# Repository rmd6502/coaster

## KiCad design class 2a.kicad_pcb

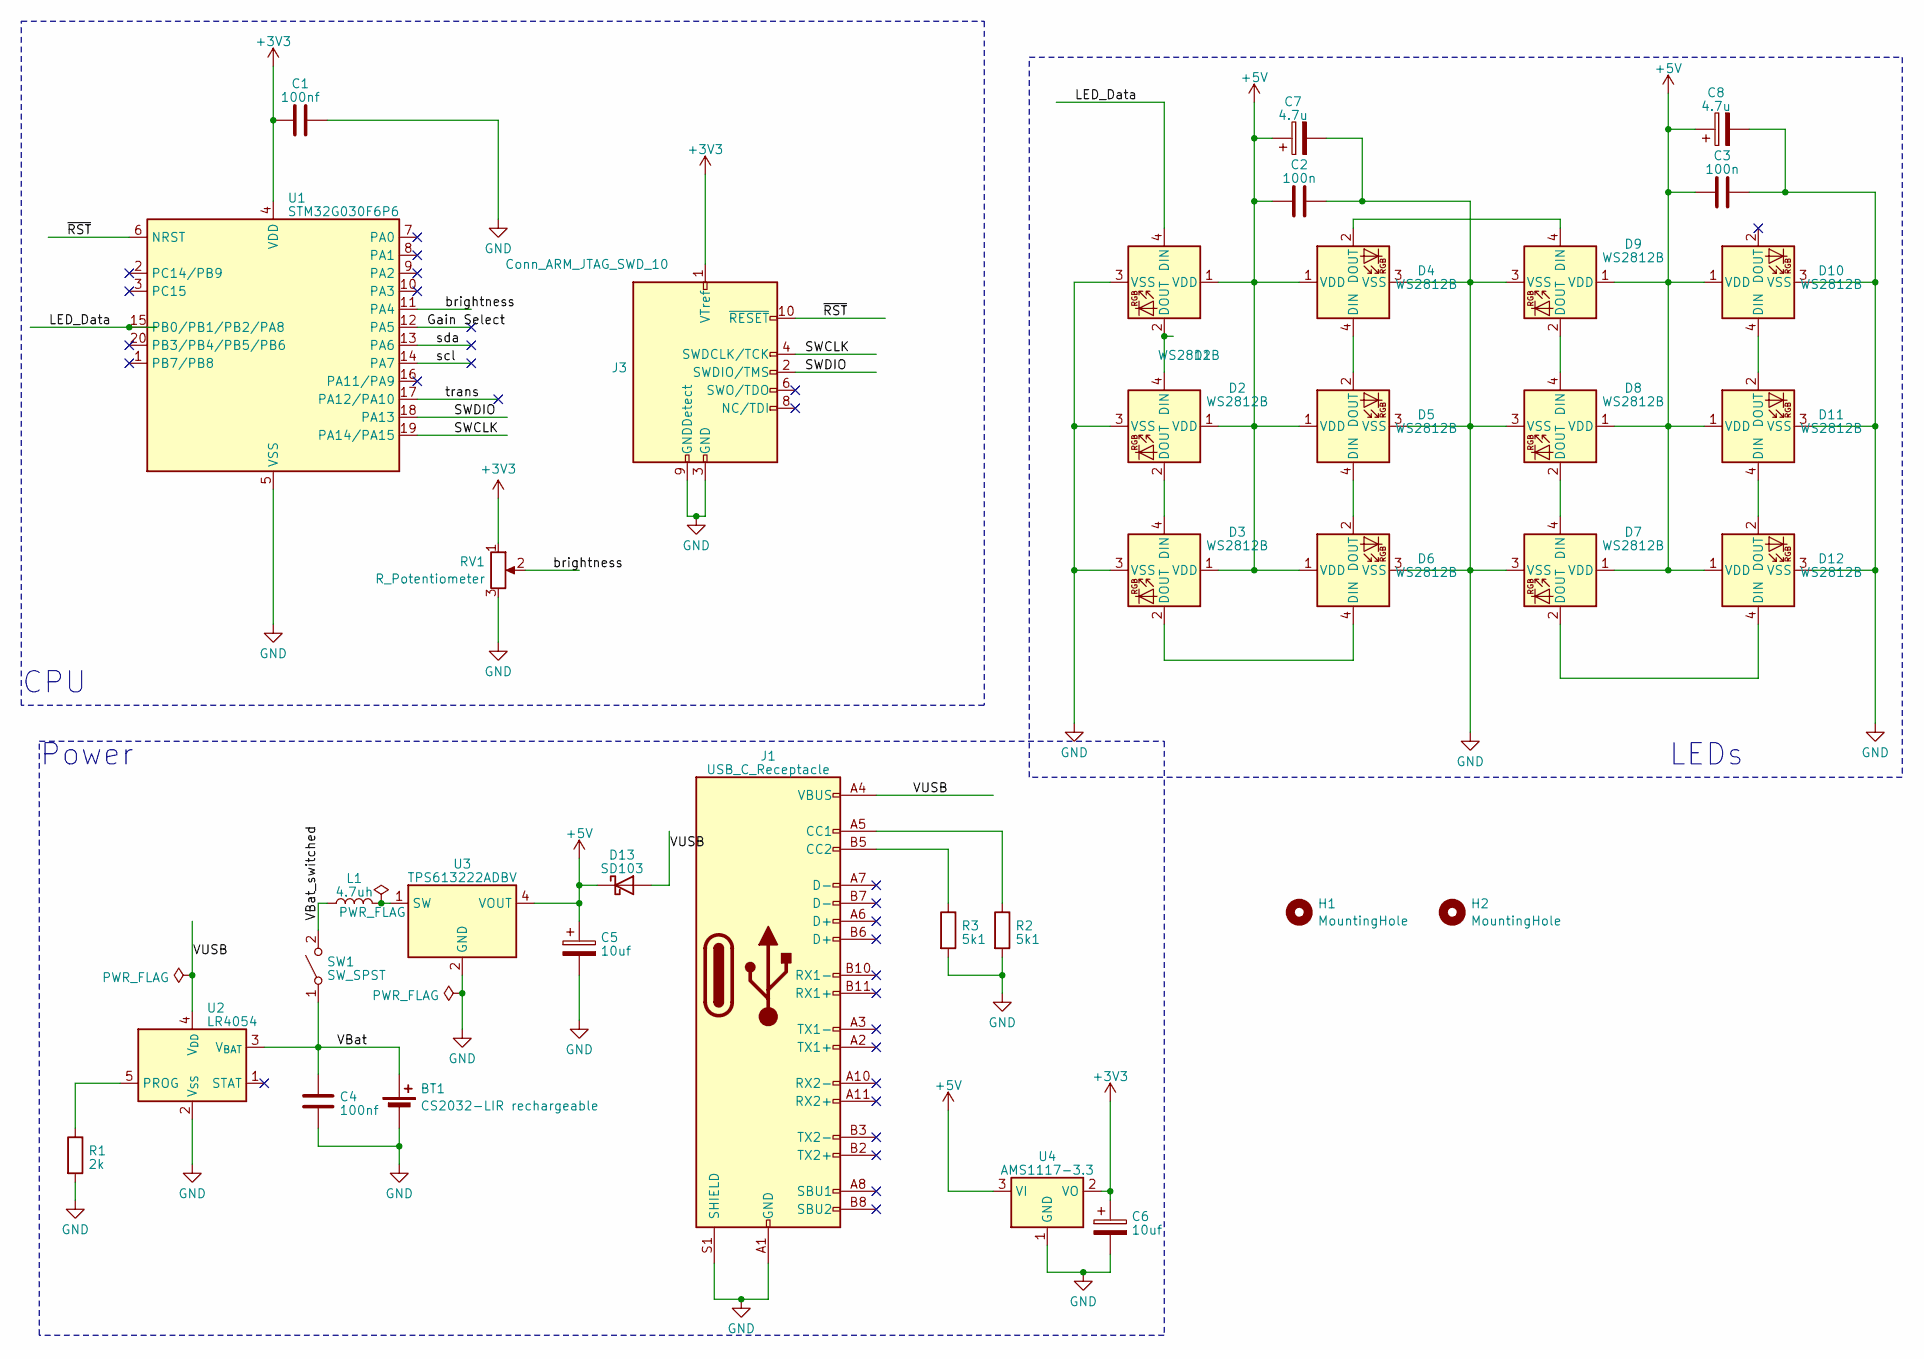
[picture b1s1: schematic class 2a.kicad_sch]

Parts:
BT1: CS2032-LIR rechargeable; BatteryHolder_Keystone_1060_1x2032
C1, C4: 100nf; C_0603_1608Metric; LCSC C14663
C2, C3: 100n; C_0603_1608Metric; LCSC C14663
C5: 10uf; CP_Elec_5x3; LCSC C249450
C6: 10uf; CP_Elec_5x3; LCSC Part C249450
C7, C8: 4.7u; CP_Elec_4x3; LCSC C249551
D1: WS2812B; LED_WS2812B_PLCC4_5.0x5.0mm_P3.2mm; LCSC Part C114586
D2, D3, D4, D5, D6, D7, D8, D9, D10, D11, D12: WS2812B; LED_WS2812B_PLCC4_5.0x5.0mm_P3.2mm; LCSC C2843785
D13: SD103; D_SOD-323F; LCSC C191023
H1, H2: MountingHole; MountingHole_2.5mm
J1: USB_C_Receptacle; USB_C_Receptacle_GCT_USB4110; LCSC Part C2927040
J3: Conn_ARM_JTAG_SWD_10; PinHeader_2x05_P1.27mm_Vertical_SMD; LCSC Part C5160761
L1: 4.7uh; L_Vishay_IHLP-2020; LCSC Part C845007
R1: 2k; R_0603_1608Metric; LCSC C25981
R2, R3: 5k1; R_0603_1608Metric; LCSC C23186
RV1: R_Potentiometer; ALPSALPINE RS08U111Z001; LCSC C202411
SW1: SW_SPST; SW_SPDT_PCM12; LCSC Part C221660
U1: STM32G030F6P6; TSSOP-20_4.4x6.5mm_P0.65mm; MPN C724040; LCSC C529330
U2: LR4054; SOT-23-5; LCSC Part C5336483
U3: TPS613222ADBV; SOT-23-5; LCSC Part C2071163
U4: AMS1117-3.3; SOT-89-3; LCSC Part C2904742

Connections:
+3V3: C1.1, C6.1, J3.1 (VTref), RV1.1, U1.4 (VDD), U4.2 (VO)
+5V: C2.1, C3.1, C5.1, C7.1, C8.1, D1.1 (VDD), D2.1 (VDD), D3.1 (VDD), D4.1 (VDD), D5.1 (VDD), D6.1 (VDD), D7.1 (VDD), D8.1 (VDD), D9.1 (VDD), D10.1 (VDD), D11.1 (VDD), D12.1 (VDD), D13.1 (K), U3.4 (VOUT), U4.3 (VI)
/Gain Select: U1.12 (PA5)
/LED_Data: D1.4 (DIN), U1.15 (PB0/PB1/PB2/PA8)
/SWCLK: J3.4 (SWDCLK/TCK), U1.19 (PA14/PA15)
/SWDIO: J3.2 (SWDIO/TMS), U1.18 (PA13)
/VBat: BT1.1 (+), C4.1, SW1.1 (A), U2.3 (V_{BAT})
/VBat_switched: L1.1, SW1.2 (B)
/VUSB: D13.2 (A), J1.A4 (VBUS), J1.A9 (VBUS), J1.B4 (VBUS), J1.B9 (VBUS), U2.4 (V_{DD})
/brightness: RV1.2, U1.11 (PA4)
/scl: U1.14 (PA7)
/sda: U1.13 (PA6)
/trans: U1.17 (PA12/PA10)
/~RST: J3.10 (~RESET), U1.6 (NRST)
GND: BT1.2 (-), C1.2, C2.2, C3.2, C4.2, C5.2, C6.2, C7.2, C8.2, D1.3 (VSS), D2.3 (VSS), D3.3 (VSS), D4.3 (VSS), D5.3 (VSS), D6.3 (VSS), D7.3 (VSS), D8.3 (VSS), D9.3 (VSS), D10.3 (VSS), D11.3 (VSS), D12.3 (VSS), J1.A1 (GND), J1.A12 (GND), J1.B1 (GND), J1.B12 (GND), J1.S1 (SHIELD), J3.3 (GND), J3.5 (GND), J3.9 (GNDDetect), R1.2, R2.2, R3.2, RV1.3, U1.5 (VSS), U2.2 (V_{SS}), U3.2 (GND), U4.1 (GND)
unnamed: D1.2 (DOUT), D2.4 (DIN)
unnamed: D2.2 (DOUT), D3.4 (DIN)
unnamed: D3.2 (DOUT), D6.4 (DIN)
unnamed: D4.4 (DIN), D5.2 (DOUT)
unnamed: D4.2 (DOUT), D9.4 (DIN)
unnamed: D5.4 (DIN), D6.2 (DOUT)
unnamed: D7.4 (DIN), D8.2 (DOUT)
unnamed: D8.4 (DIN), D9.2 (DOUT)
unnamed: D10.4 (DIN), D11.2 (DOUT)
unnamed: D11.4 (DIN), D12.2 (DOUT)
unnamed: D7.2 (DOUT), D12.4 (DIN)
unnamed: J1.A5 (CC1), R2.1
unnamed: J1.B5 (CC2), R3.1
unnamed: R1.1, U2.5 (PROG)
unnamed: L1.2, U3.1 (SW)

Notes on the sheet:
Power
CPU
LEDs

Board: 2 copper layers, 36 parts (7 on the bottom side), 26 nets, no tracks yet.

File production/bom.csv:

Designator,Footprint,Quantity,Value,LCSC Part #
"C1, C4",0603,2,100nf,
"C2, C3",0603,2,100n,
"C5, C6",CP_Elec_5x3,2,10uf,C249450
"C7, C8",CP_Elec_4x3,2,4.7u,C249551
"D1, D10, D11, D12, D2, D3, D4, D5, D6, D7, D8, D9",LED_WS2812B_PLCC4_5.0x5.0mm_P3.2mm,12,WS2812B,C114586
J1,USB_C_Receptacle_HRO_TYPE-C-31-M-12,1,USB_C_Receptacle,C165948
J2,JST_PH_S2B-PH-K_1x02_P2.00mm_Horizontal,1,Conn_01x02_Pin,C173752
J3,PinHeader_2x05_P1.27mm_Vertical_SMD,1,Conn_ARM_JTAG_SWD_10,C180221
L1,L_Vishay_IHLP-2020,1,4.7uh,C845007
R1,0603,1,2k,
R2,0603,1,5k1,
SW1,SW_SPDT_CK-JS102011SAQN,1,SW_SPST,C221660
U1,TSSOP-20_4.4x6.5mm_P0.65mm,1,STM32G030F6P6,C724040
U2,SOT-23-5,1,LR4054,C5336483
U3,SOT-23-5,1,TPS613222ADBV,C2071163
U4,SOT-89-3,1,AMS1117-3.3,C2904742

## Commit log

2023-05-02 initial
2023-05-02 add gitignore
2023-05-02 add image
2023-05-03 add power switch, cleanups
2023-05-12 update board to use instrumentation amp
2023-05-24 production
2023-07-15 fix drc and erc
2023-07-15 move battery connector to bottom
2024-07-01 heart
2024-10-25 fix resistors for usb-c
2024-10-25 rearrange things and use CR2032LIR
